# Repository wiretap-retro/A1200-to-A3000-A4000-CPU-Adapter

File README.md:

# A1200 to A3000/A4000 CPU Adapter
An adapter to use an A1200 CPU in an Amiga 3000 or 4000. Targed for Pistorm32 use only.

## Info
Do not build. Preliminary rev for test purposes only. May not work. Included in the repository are the KiCAD v5 footprints and symbols for the A1200 and A4000 connectors. Autorouted traces and it requires schematic verification. Measurements of the rough PCB outline are not verified. The intent of this connector is to adapt the Pistorm32 for use in the Amiga 4000, possibly the Amiga 3000. It is not known if it will work yet..

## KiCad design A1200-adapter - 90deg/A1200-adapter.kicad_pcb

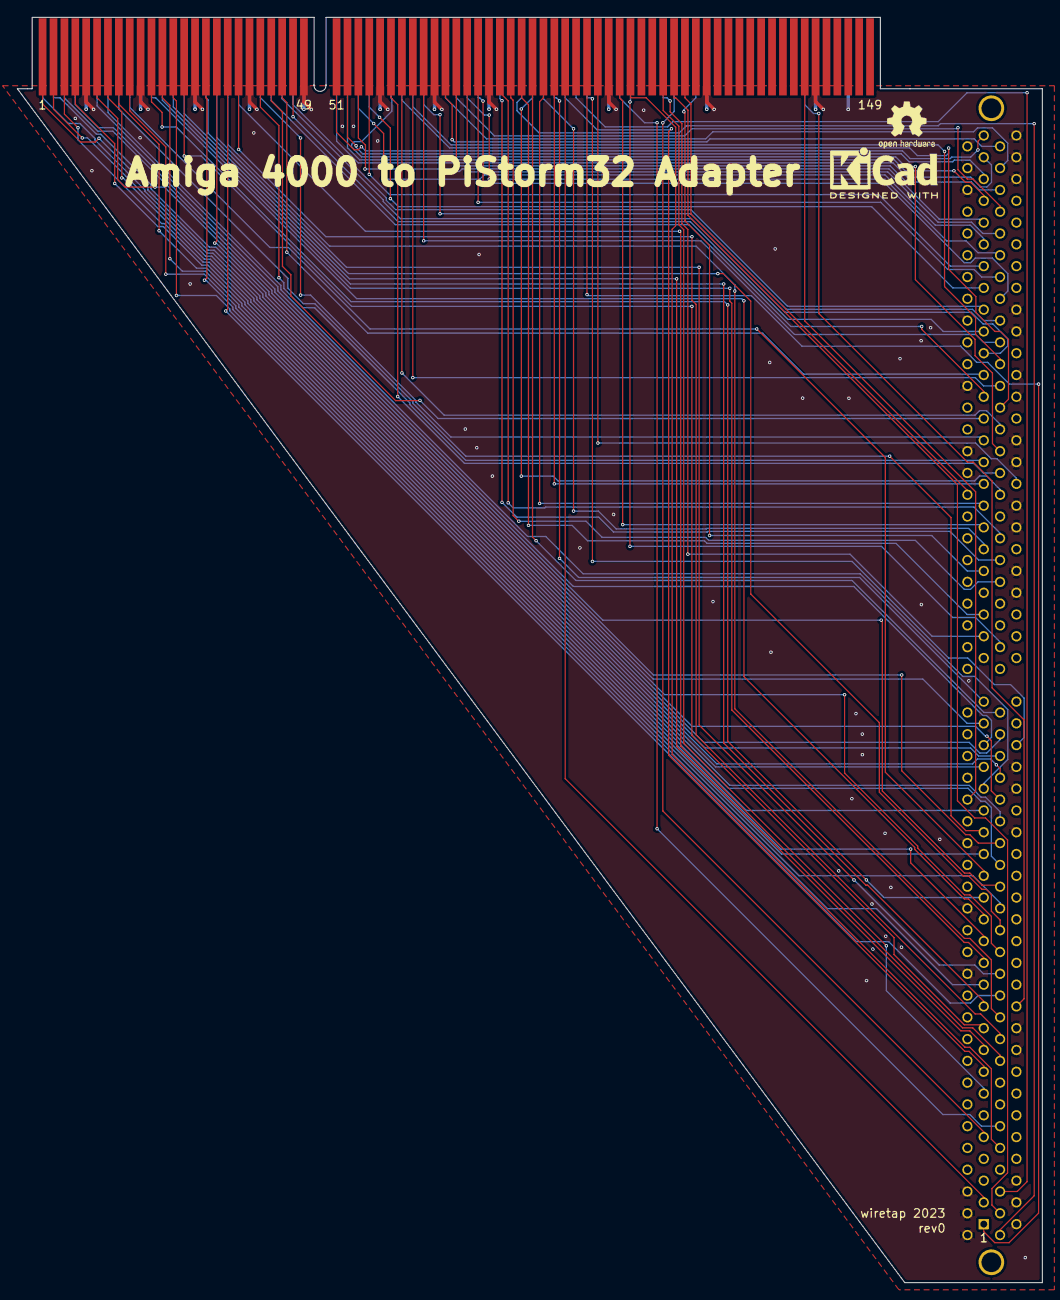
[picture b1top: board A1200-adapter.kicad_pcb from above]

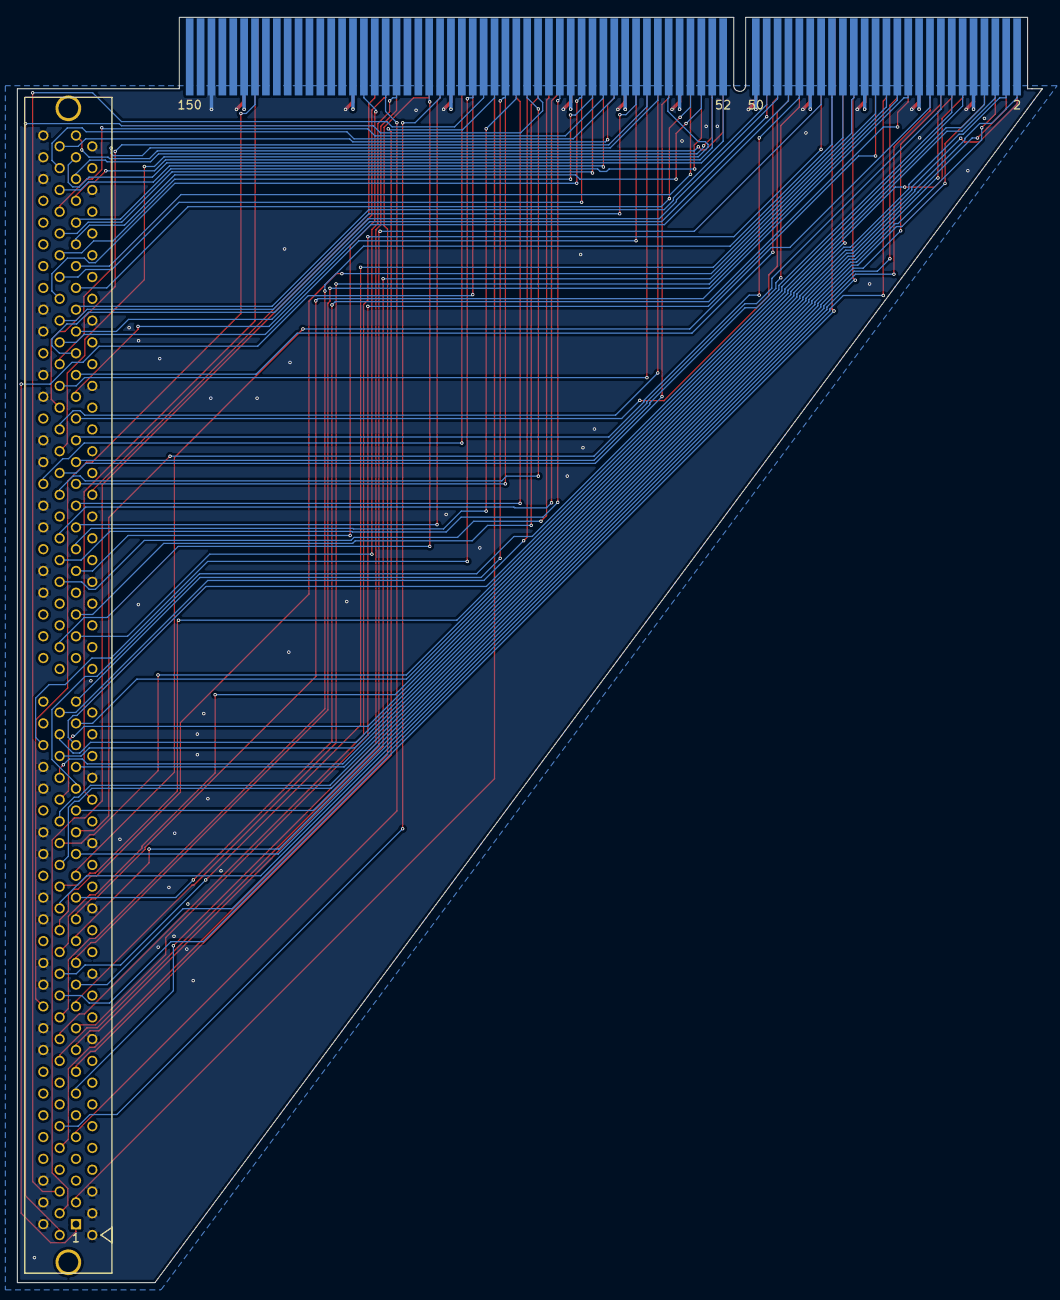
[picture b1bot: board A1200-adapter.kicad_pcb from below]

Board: 4 copper layers, 119.6 x 147.6 mm, 4 parts (2 on the bottom side), 95 nets.

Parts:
CON1: A3000_A4000_LOCAL_BUS_SLOT; KEL-8817-200-170S-F
CON2: A1200-EXP
Kicad-Logo: KiCad-Logo2_5mm_SilkScreen
OSHW-logo: OSHW-Logo2_7.3x6mm_SilkScreen

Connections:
+5V: CON1.14, CON1.15, CON1.18, CON1.19, CON1.22, CON1.23, CON1.26, CON1.27, CON1.94, CON1.95, CON1.98, CON1.99, CON1.102, CON1.103, CON1.106, CON1.107, CON1.174, CON1.175, CON1.178, CON1.179, CON1.182, CON1.183, CON1.186, CON1.187, CON2.10, CON2.20, CON2.30, CON2.40, CON2.50, CON2.60, CON2.70, CON2.80, CON2.102, CON2.120, CON2.140
/A0: CON1.36, CON2.38
/A1: CON1.40, CON2.37
/A2: CON1.44, CON2.36
/A3: CON1.48, CON2.35
/A4: CON1.52, CON2.34
/A5: CON1.56, CON2.33
/A6: CON1.60, CON2.32
/A7: CON1.64, CON2.31
/A8: CON1.33, CON2.28
/A9: CON1.37, CON2.27
/A10: CON1.41, CON2.26
/A11: CON1.45, CON2.25
/A12: CON1.49, CON2.24
/A13: CON1.53, CON2.23
/A14: CON1.57, CON2.22
/A15: CON1.61, CON2.21
/A16: CON1.65, CON2.18
/A17: CON1.69, CON2.17
/A18: CON1.73, CON2.16
/A19: CON1.77, CON2.15
/A20: CON1.81, CON2.14
/A21: CON1.85, CON2.13
/A22: CON1.89, CON2.12
/A23: CON1.93, CON2.11
/A24: CON1.68, CON2.8
/A25: CON1.72, CON2.7
/A26: CON1.76, CON2.6
/A27: CON1.80, CON2.5
/A28: CON1.84, CON2.4
/A29: CON1.88, CON2.3
/A30: CON1.92, CON2.2
/A31: CON1.96, CON2.1
/AS: CON1.133, CON2.91
/AVEC: CON1.12, CON2.96
/BERR: CON1.29, CON2.94
/BG: CON1.105, CON2.112
/BGACK: CON1.8, CON2.113
/BOSS: CON1.17, CON2.114
/BR: CON1.25, CON2.111
/CPUCLK: CON1.135, CON2.99
/D0: CON1.172, CON2.78
/D1: CON1.176, CON2.77
/D2: CON1.180, CON2.76
/D3: CON1.184, CON2.75
/D4: CON1.188, CON2.74
/D5: CON1.192, CON2.73
/D6: CON1.196, CON2.72
/D7: CON1.200, CON2.71
/D8: CON1.168, CON2.68
/D9: CON1.164, CON2.67
/D10: CON1.160, CON2.66
/D11: CON1.156, CON2.65
/D12: CON1.152, CON2.64
/D13: CON1.148, CON2.63
/D14: CON1.144, CON2.62
/D15: CON1.140, CON2.61
/D16: CON1.169, CON2.58
/D17: CON1.173, CON2.57
/D18: CON1.177, CON2.56
/D19: CON1.181, CON2.55
/D20: CON1.185, CON2.54
/D21: CON1.189, CON2.53
/D22: CON1.193, CON2.52
/D23: CON1.197, CON2.51
/D24: CON1.165, CON2.48
/D25: CON1.161, CON2.47
/D26: CON1.157, CON2.46
/D27: CON1.153, CON2.45
/D28: CON1.149, CON2.44
/D29: CON1.145, CON2.43
/D30: CON1.141, CON2.42
/D31: CON1.137, CON2.41
/DS: CON1.97, CON2.92
/DSACK0: CON1.91, CON2.98
/DSACK1: CON1.1, CON2.97
/ECS: CON1.100, CON2.87
/FC0: CON1.20, CON2.105
/FC1: CON1.24, CON2.104
/FC2: CON1.125, CON2.103
/FPUCS: CON1.134, CON2.115
/HLT: CON1.4, CON2.86
/INT2: CON1.82, CON2.137
/INT6: CON1.43, CON2.138
/IPL0: CON1.120, CON2.83
/IPL1: CON1.124, CON2.82
/IPL2: CON1.128, CON2.81
/OCS: CON1.136, CON2.88
/RESET: CON1.117, CON2.118
/RMC: CON1.108, CON2.106
/RST: CON1.109, CON2.85
/RW: CON1.5, CON2.93
/SIZ0: CON1.121, CON2.90
/SIZ1: CON1.129, CON2.89
GND: CON1.2, CON1.3, CON1.6, CON1.7, CON1.10, CON1.11, CON1.35, CON1.38, CON1.39, CON1.47, CON1.50, CON1.51, CON1.59, CON1.62, CON1.63, CON1.71, CON1.74, CON1.75, CON1.83, CON1.86, CON1.87, CON1.115, CON1.118, CON1.119, CON1.127, CON1.130, CON1.131, CON1.138, CON1.139, CON1.142, CON1.143, CON1.151, CON1.154, CON1.155, CON1.163, CON1.166, CON1.167, CON1.190, CON1.191, CON1.194, CON1.195, CON1.198, CON1.199, CON2.9, CON2.19, CON2.29, CON2.39, CON2.49, CON2.59, CON2.69, CON2.79, CON2.101, CON2.119, CON2.139, CON2.146
